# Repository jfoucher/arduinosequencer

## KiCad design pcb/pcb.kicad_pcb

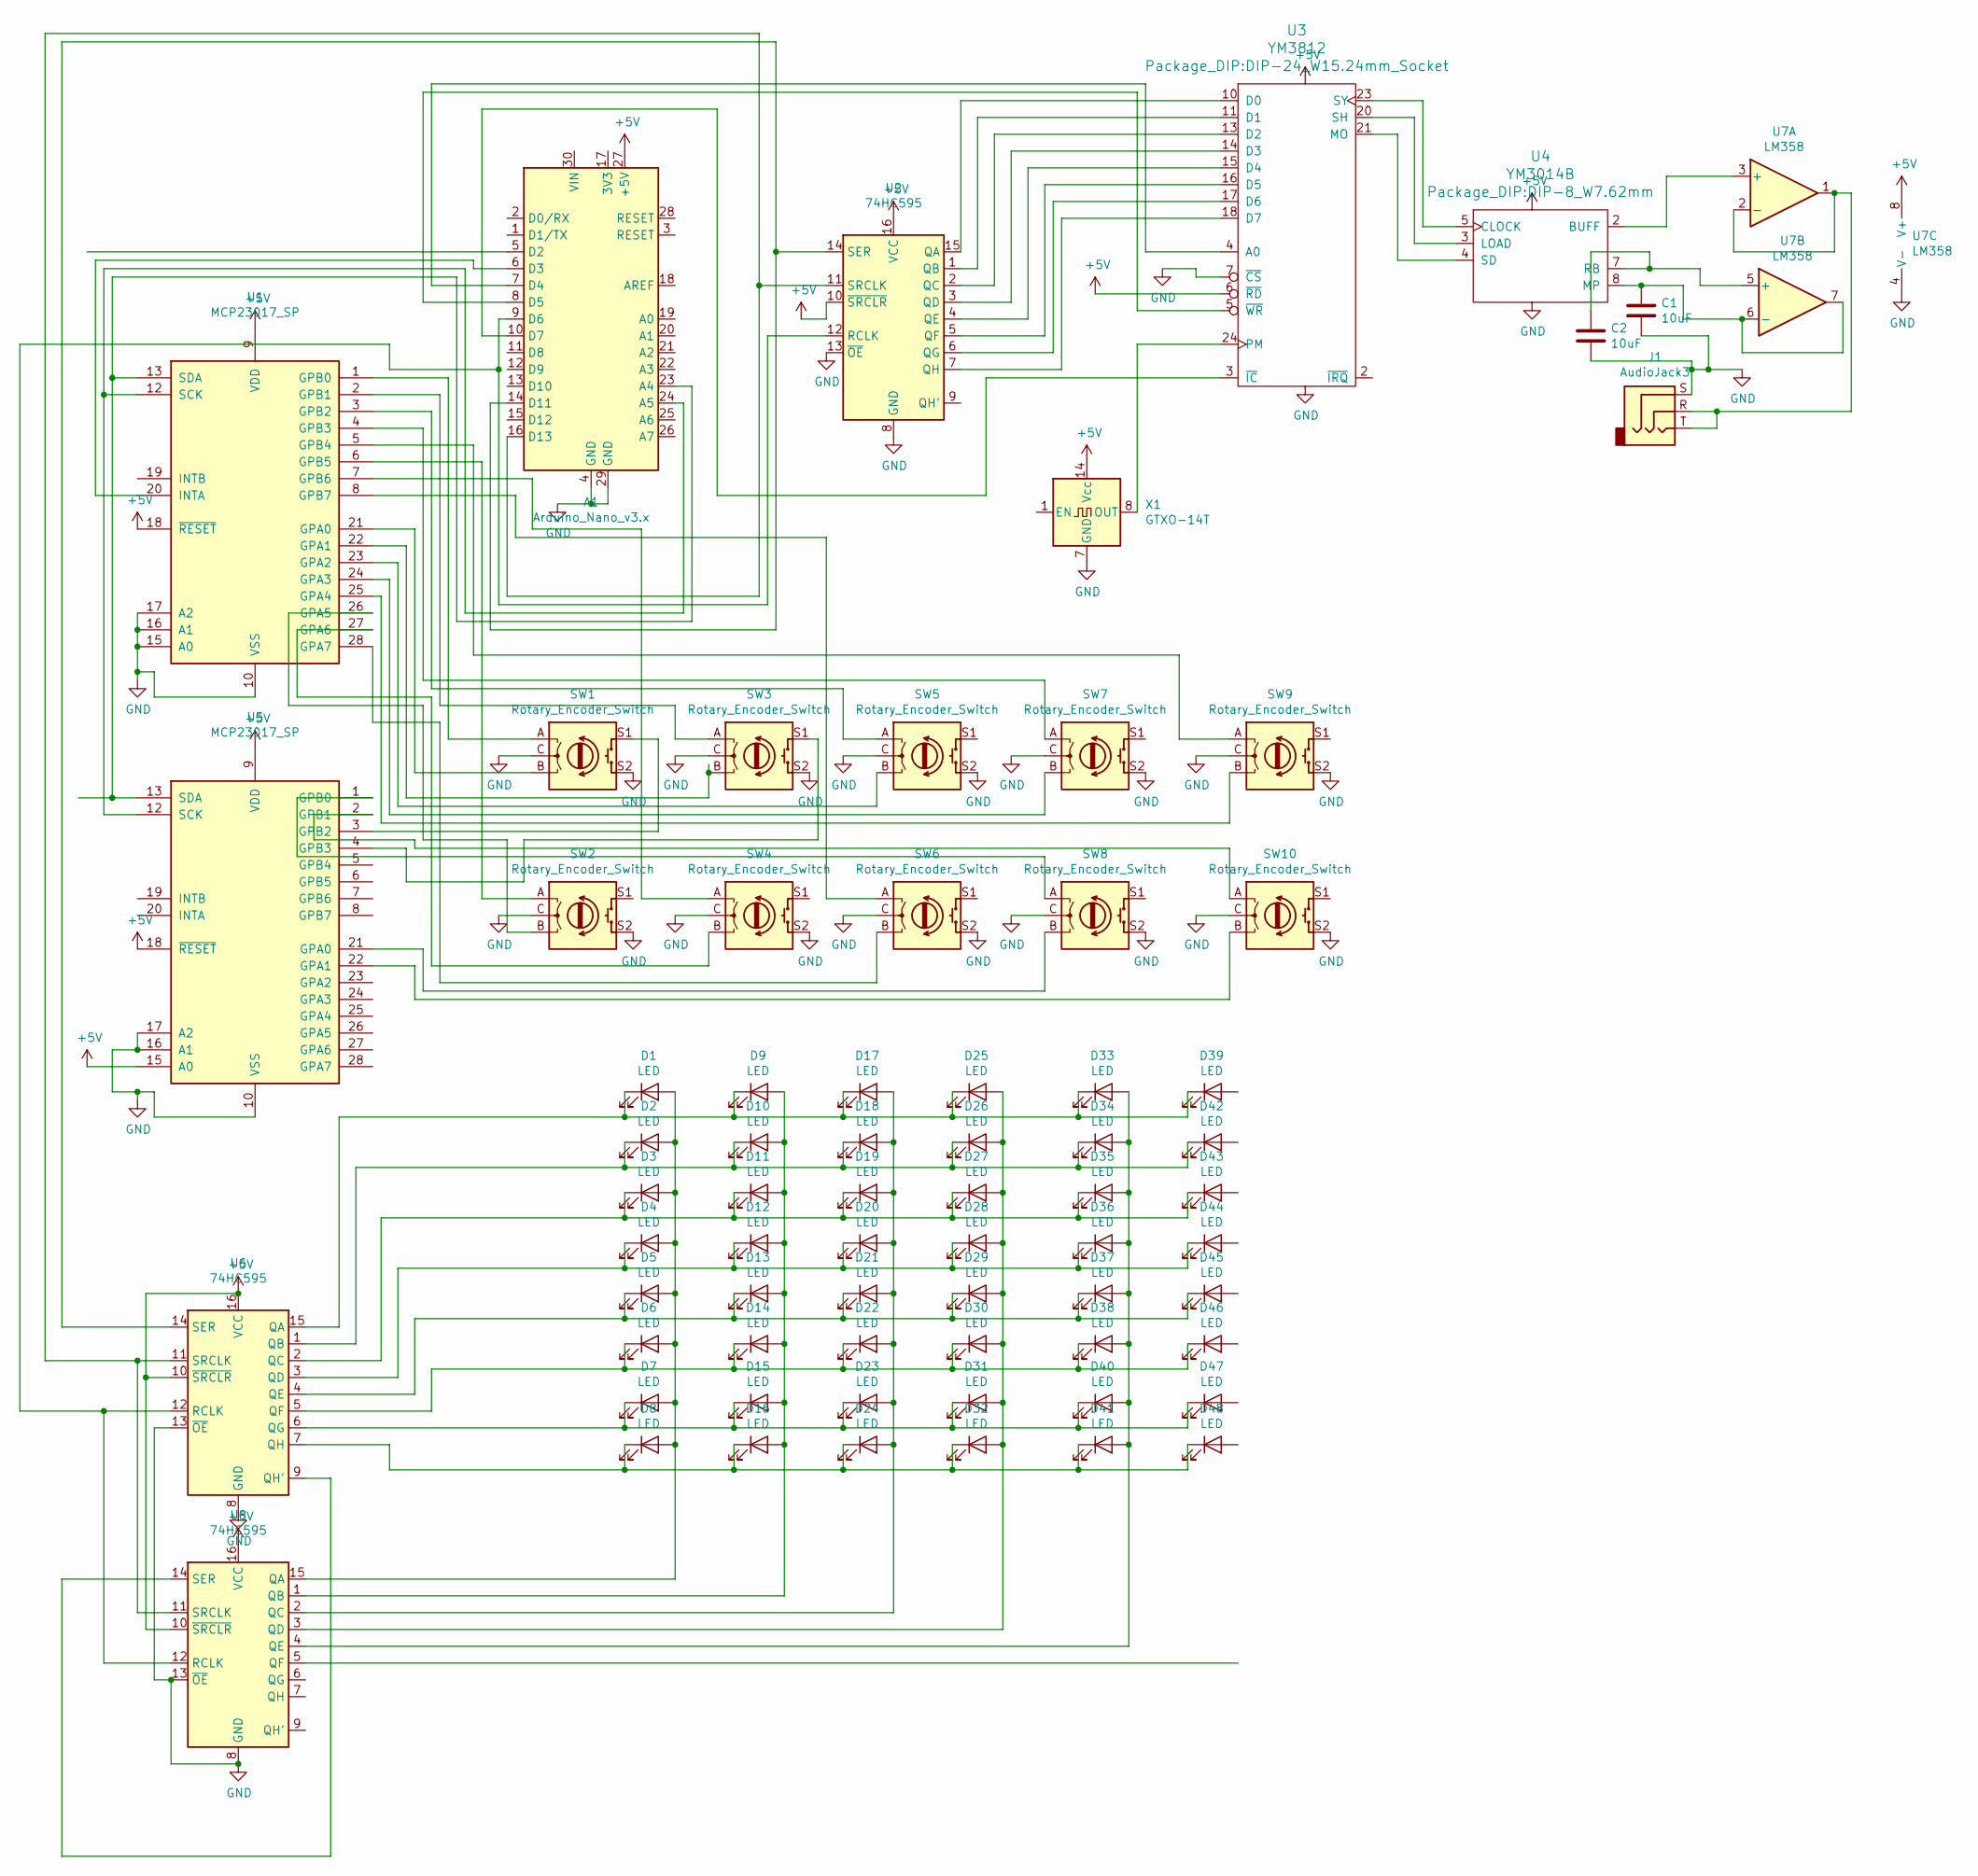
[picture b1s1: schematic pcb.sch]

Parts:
A1: Arduino_Nano_v3.x; Arduino_Nano
C1, C2: 10uF; C_Disc_D3.8mm_W2.6mm_P2.50mm
D1, D2, D3, D4, D5, D6, D7, D8, D9, D10, D11, D12, D13, D14, D15, D16, D17, D18, D19, D20, D21, D22, D23, D24, D25, D26, D27, D28, D29, D30, D31, D32, D33, D34, D35, D36, D37, D38, D39, D40, D41, D42, D43, D44, D45, D46, D47, D48: LED; LED_D3.0mm
J1: AudioJack3; Jack_3.5mm_CUI_SJ1-3533NG_Horizontal
SW1, SW2, SW3, SW4, SW5, SW6, SW7, SW8, SW9, SW10: Rotary_Encoder_Switch; RotaryEncoder_Alps_EC12E-Switch_Vertical_H20mm
U1, U5: MCP23017_SP; DIP-28_W7.62mm_Socket
U2, U6, U8: 74HC595; DIP-16_W7.62mm_Socket
U3: YM3812; DIP-24_W15.24mm_Socket
U4: YM3014B; DIP-8_W7.62mm
U7: LM358; DIP-8_W7.62mm_Socket
X1: GTXO-14T; Oscillator_DIP-14

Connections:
+5V: A1.27 (+5V), U1.9 (VDD), U1.18 (~RESET~), U2.10 (~SRCLR), U2.16 (VCC), U3.1 (VCC), U3.6 (~RD), U4.1 (VCC), U5.9 (VDD), U5.15 (A0), U5.18 (~RESET~), U6.10 (~SRCLR), U6.16 (VCC), U7.8 (V+), U8.10 (~SRCLR), U8.16 (VCC), X1.14 (Vcc)
GND: A1.4 (GND), A1.29 (GND), C1.2, C2.2, J1.S, SW1.C, SW1.S2, SW2.C, SW2.S2, SW3.C, SW3.S2, SW4.C, SW4.S2, SW5.C, SW5.S2, SW6.C, SW6.S2, SW7.C, SW7.S2, SW8.C, SW8.S2, SW9.C, SW9.S2, SW10.C, SW10.S2, U1.10 (VSS), U1.15 (A0), U1.16 (A1), U1.17 (A2), U2.8 (GND), U2.13 (~OE), U3.7 (~CS), U3.12 (GND), U4.6 (GND), U5.10 (VSS), U5.16 (A1), U5.17 (A2), U6.8 (GND), U6.13 (~OE), U7.4 (V-), U8.8 (GND), U8.13 (~OE), X1.7 (GND)
unnamed: A1.6 (D3), U1.20 (INTA)
unnamed: A1.7 (D4), U3.4 (A0)
unnamed: A1.8 (D5), U3.5 (~WR)
unnamed: A1.9 (D6), U2.12 (RCLK), U6.12 (RCLK), U8.12 (RCLK)
unnamed: A1.10 (D7), U3.3 (~IC)
unnamed: A1.14 (D11), U2.14 (SER), U6.14 (SER)
unnamed: A1.16 (D13), U2.11 (SRCLK), U6.11 (SRCLK), U8.11 (SRCLK)
unnamed: A1.23 (A4), U1.13 (SDA), U5.13 (SDA)
unnamed: A1.24 (A5), U1.12 (SCK), U5.12 (SCK)
unnamed: C1.1, U4.8 (MP), U7.6 (-), U7.7
unnamed: C2.1, U4.7 (RB), U7.5 (+)
unnamed: D1.1 (K), D9.1 (K), D17.1 (K), D25.1 (K), D33.1 (K), D39.1 (K), U6.15 (QA)
unnamed: D1.2 (A), D2.2 (A), D3.2 (A), D4.2 (A), D5.2 (A), D6.2 (A), D7.2 (A), D8.2 (A), U8.15 (QA)
unnamed: D2.1 (K), D10.1 (K), D18.1 (K), D26.1 (K), D34.1 (K), D42.1 (K), U6.1 (QB)
unnamed: D9.2 (A), D10.2 (A), D11.2 (A), D12.2 (A), D13.2 (A), D14.2 (A), D15.2 (A), D16.2 (A), U8.1 (QB)
unnamed: D3.1 (K), D11.1 (K), D19.1 (K), D27.1 (K), D35.1 (K), D43.1 (K), U6.2 (QC)
unnamed: D4.1 (K), D12.1 (K), D20.1 (K), D28.1 (K), D36.1 (K), D44.1 (K), U6.3 (QD)
unnamed: D5.1 (K), D13.1 (K), D21.1 (K), D29.1 (K), D37.1 (K), D45.1 (K), U6.4 (QE)
unnamed: D6.1 (K), D14.1 (K), D22.1 (K), D30.1 (K), D38.1 (K), D46.1 (K), U6.5 (QF)
unnamed: D7.1 (K), D15.1 (K), D23.1 (K), D31.1 (K), D40.1 (K), D47.1 (K), U6.6 (QG)
unnamed: D8.1 (K), D16.1 (K), D24.1 (K), D32.1 (K), D41.1 (K), D48.1 (K), U6.7 (QH)
unnamed: D17.2 (A), D18.2 (A), D19.2 (A), D20.2 (A), D21.2 (A), D22.2 (A), D23.2 (A), D24.2 (A), U8.2 (QC)
unnamed: D25.2 (A), D26.2 (A), D27.2 (A), D28.2 (A), D29.2 (A), D30.2 (A), D31.2 (A), D32.2 (A), U8.3 (QD)
unnamed: D33.2 (A), D34.2 (A), D35.2 (A), D36.2 (A), D37.2 (A), D38.2 (A), D40.2 (A), D41.2 (A), U8.4 (QE)
unnamed: J1.R, J1.T, U7.1, U7.2 (-)
unnamed: SW1.A, U1.1 (GPB0)
unnamed: SW1.B, U1.21 (GPA0)
unnamed: SW1.S1, U5.3 (GPB2)
unnamed: SW2.A, U1.6 (GPB5)
unnamed: SW2.B, U1.26 (GPA5)
unnamed: SW3.A, U1.2 (GPB1)
unnamed: SW3.B, U1.22 (GPA1)
unnamed: SW3.S1, U5.4 (GPB3)
unnamed: SW4.A, U1.7 (GPB6)
unnamed: SW4.B, U1.27 (GPA6)
unnamed: SW5.A, U1.3 (GPB2)
unnamed: SW5.B, U1.23 (GPA2)
unnamed: SW6.A, U1.8 (GPB7)
unnamed: SW6.B, U1.28 (GPA7)
unnamed: SW7.A, U1.4 (GPB3)
unnamed: SW7.B, U1.24 (GPA3)
unnamed: SW8.A, U5.1 (GPB0)
unnamed: SW8.B, U5.21 (GPA0)
unnamed: SW9.A, U1.5 (GPB4)
unnamed: SW9.B, U1.25 (GPA4)
unnamed: SW10.A, U5.2 (GPB1)
unnamed: SW10.B, U5.22 (GPA1)
unnamed: U2.1 (QB), U3.11 (D1)
unnamed: U2.2 (QC), U3.13 (D2)
unnamed: U2.3 (QD), U3.14 (D3)
unnamed: U2.4 (QE), U3.15 (D4)
unnamed: U2.5 (QF), U3.16 (D5)
unnamed: U2.6 (QG), U3.17 (D6)
unnamed: U2.7 (QH), U3.18 (D7)
unnamed: U2.15 (QA), U3.10 (D0)
unnamed: U3.20 (SH), U4.3 (LOAD)
unnamed: U3.21 (MO), U4.4 (SD)
unnamed: U3.23 (SY), U4.5 (CLOCK)
unnamed: U3.24 (PM), X1.8 (OUT)
unnamed: U4.2 (BUFF), U7.3 (+)
unnamed: U6.9 (QH'), U8.14 (SER)

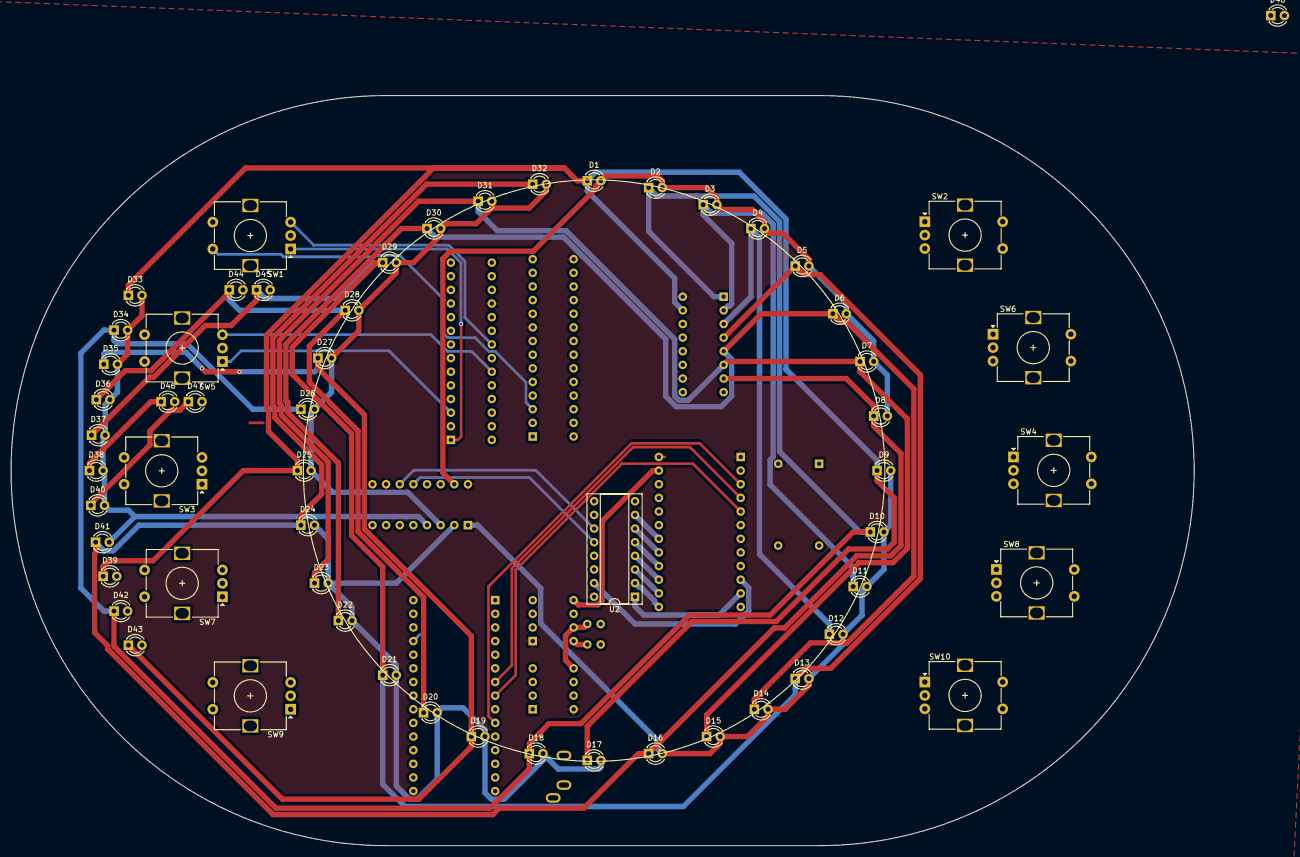
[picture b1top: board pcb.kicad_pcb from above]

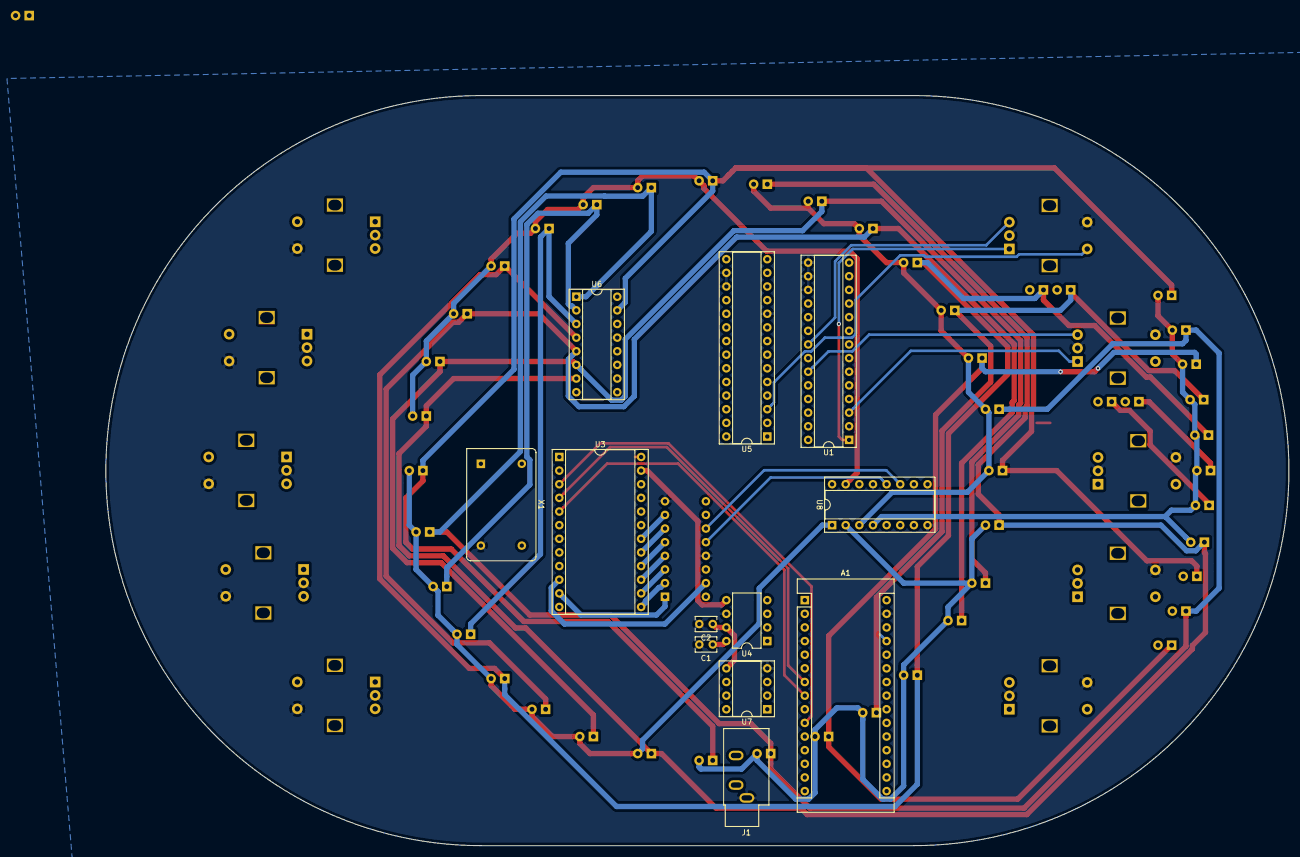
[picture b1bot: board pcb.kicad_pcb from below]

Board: 2 copper layers, 220.3 x 139.7 mm, 71 parts (12 on the bottom side), 63 nets.

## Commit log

2019-10-13 Change tempo handling
2020-01-21 refactor reading rotary encoders
2020-01-22 Make use of interrupts to handle rotary encoders and switches
2020-01-22 Can save and restore from eeprom
2020-01-22 Play inside interrupt handler, remove tempo led
2020-01-22 flash led in loop
2020-01-23 use 74HC595 and spi to display leds
2020-01-23 add kicad pcb
2020-01-27 Handle more encoders and switches
2020-01-27 If the current step has a sound, make led brighter
2020-01-28 More encoders. Reduce memory usage
2020-02-01 New pcb and schematic
